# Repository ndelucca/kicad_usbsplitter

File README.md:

# kicad_usbsplitter
Personal design for a 3-way usb splitter

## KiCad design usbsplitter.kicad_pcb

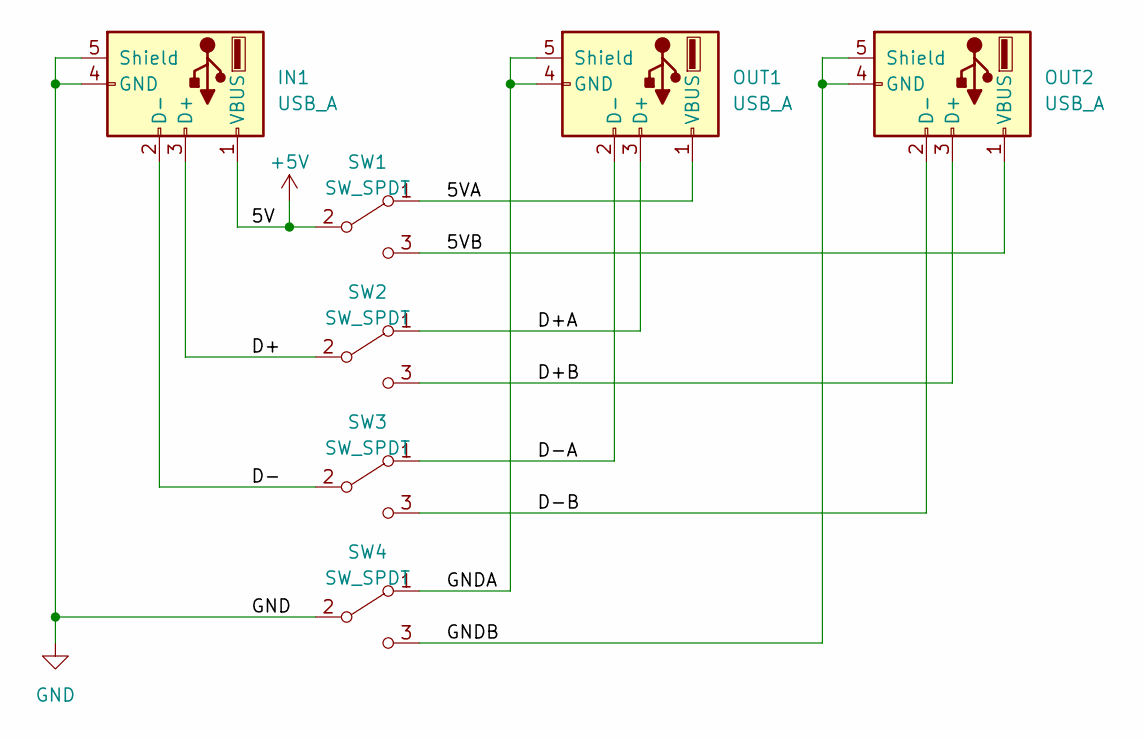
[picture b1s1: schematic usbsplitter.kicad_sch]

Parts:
IN1: USB_A; USB_A_CONNFLY_DS1095-WNR0
OUT1, OUT2: USB_A; USB_A_CONNFLY_DS1095-WNR0
SW1, SW2, SW3, SW4: SW_SPDT; PinHeader_1x03_P2.54mm_Vertical

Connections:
+5V: IN1.1 (VBUS), SW1.2 (B)
/5VA: OUT1.1 (VBUS), SW1.1 (A)
/5VB: OUT2.1 (VBUS), SW1.3 (C)
/D+: IN1.3 (D+), SW2.2 (B)
/D+A: OUT1.3 (D+), SW2.1 (A)
/D+B: OUT2.3 (D+), SW2.3 (C)
/D-: IN1.2 (D-), SW3.2 (B)
/D-A: OUT1.2 (D-), SW3.1 (A)
/D-B: OUT2.2 (D-), SW3.3 (C)
/GNDA: OUT1.4 (GND), OUT1.5 (Shield), SW4.1 (A)
/GNDB: OUT2.4 (GND), OUT2.5 (Shield), SW4.3 (C)
GND: IN1.4 (GND), IN1.5 (Shield), SW4.2 (B)

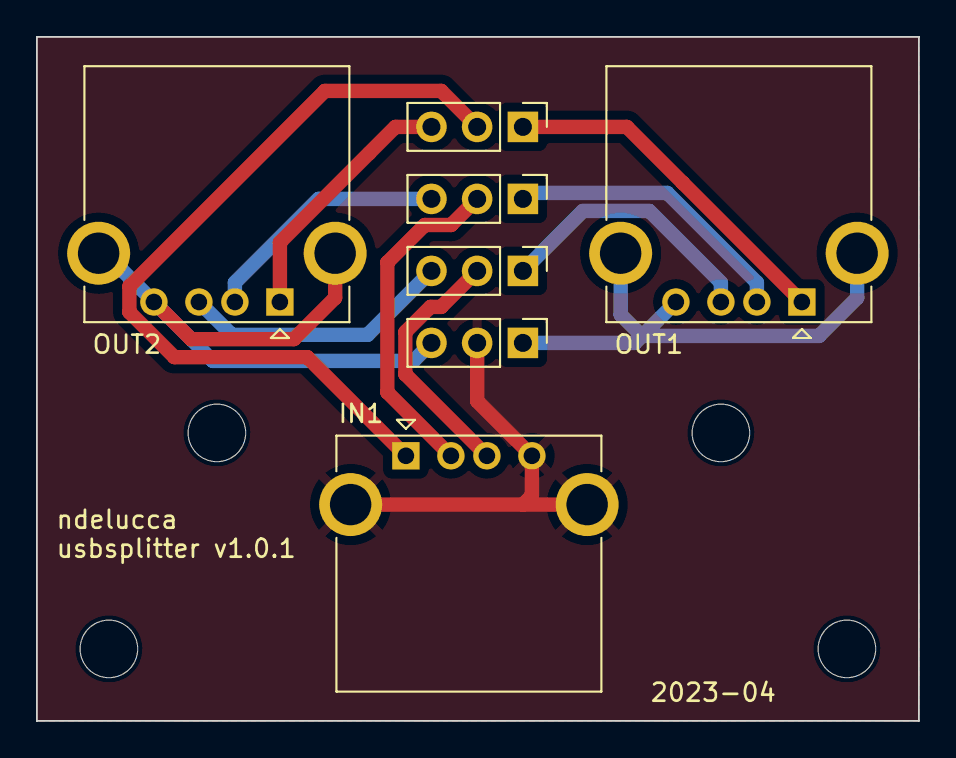
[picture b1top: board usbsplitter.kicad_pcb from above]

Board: 2 copper layers, 49.0 x 38.0 mm, 7 parts (0 on the bottom side), 12 nets.

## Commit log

2023-03-19 initialize repository
2023-04-22 v1.0.0
2023-04-22 v1.0.1
